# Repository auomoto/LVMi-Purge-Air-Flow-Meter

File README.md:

# LVMi Purge Air Flow Meter
 Differential Pressure Sensor for LVMi Purge Air Flow

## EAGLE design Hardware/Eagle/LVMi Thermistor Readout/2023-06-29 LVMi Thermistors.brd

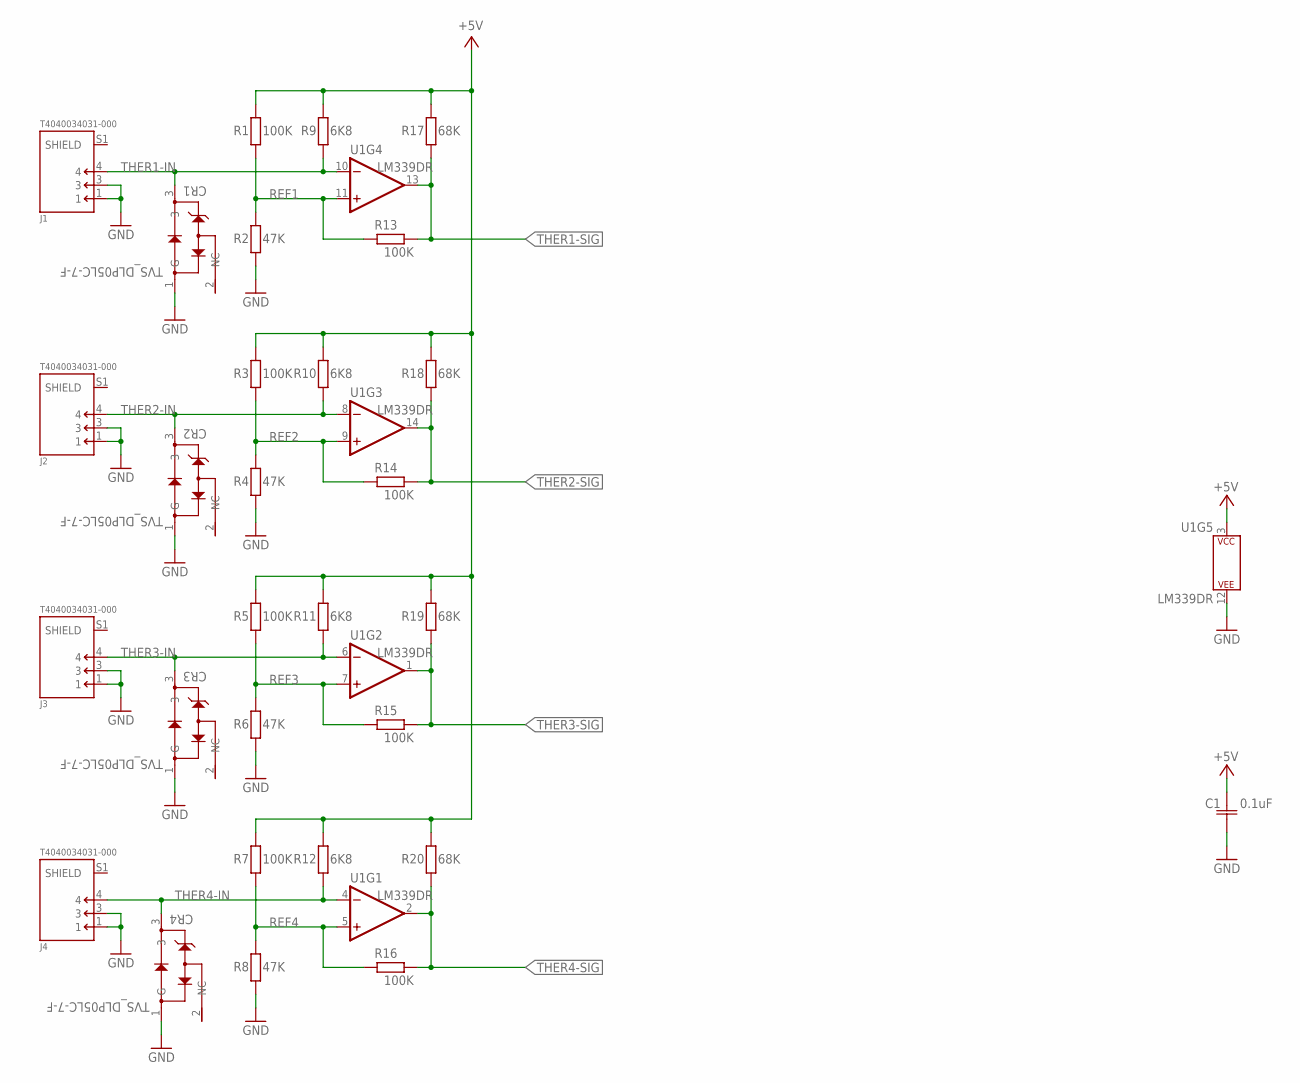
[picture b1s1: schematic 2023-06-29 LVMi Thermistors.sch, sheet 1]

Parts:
C1: 0.1uF; K104K15X7RF5TL2_VIS
CR1, CR2, CR3, CR4: TVS_DLP05LC-7-F; SOT23_DLP05LC_DIO
J1, J2, J3, J4: T4040034031-000; TE_T4040034031-000
R1, R3, R5, R7, R13, R14, R15, R16: 100K; 0207/10
R2, R4, R6, R8: 47K; 0207/10
R9, R10, R11, R12: 6K8; 0207/10
R17, R18, R19, R20: 68K; 0207/10
U1: LM339DR; SOIC127P599X175-14

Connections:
+5V: C1.2, R1.2, R3.2, R5.2, R7.2, R9.2, R10.2, R11.2, R12.2, R17.2, R18.2, R19.2, R20.2, U1.3 (P$V+); also elsewhere on the board
GND: C1.1, CR1.1 (G), CR2.1 (G), CR3.1 (G), CR4.1 (G), J1.1, J1.3, J2.1, J2.3, J3.1, J3.3, J4.1, J4.3, R2.1, R4.1, R6.1, R8.1, U1.12 (P$V-); also elsewhere on the board
REF1: R1.1, R2.2, R13.2, U1.11 (+IN)
REF2: R3.1, R4.2, R14.2, U1.9 (+IN)
REF3: R5.1, R6.2, R15.2, U1.7 (+IN)
REF4: R7.1, R8.2, R16.2, U1.5 (+IN)
THER1-IN: CR1.3, J1.4, R9.1, U1.10 (-IN)
THER1-SIG: R13.1, R17.1, U1.13 (OUT); also elsewhere on the board
THER2-IN: CR2.3, J2.4, R10.1, U1.8 (-IN)
THER2-SIG: R14.1, R18.1, U1.14 (OUT); also elsewhere on the board
THER3-IN: CR3.3, J3.4, R11.1, U1.6 (-IN)
THER3-SIG: R15.1, R19.1, U1.1 (OUT); also elsewhere on the board
THER4-IN: CR4.3, J4.4, R12.1, U1.4 (-IN)
THER4-SIG: R16.1, R20.1, U1.2 (OUT); also elsewhere on the board

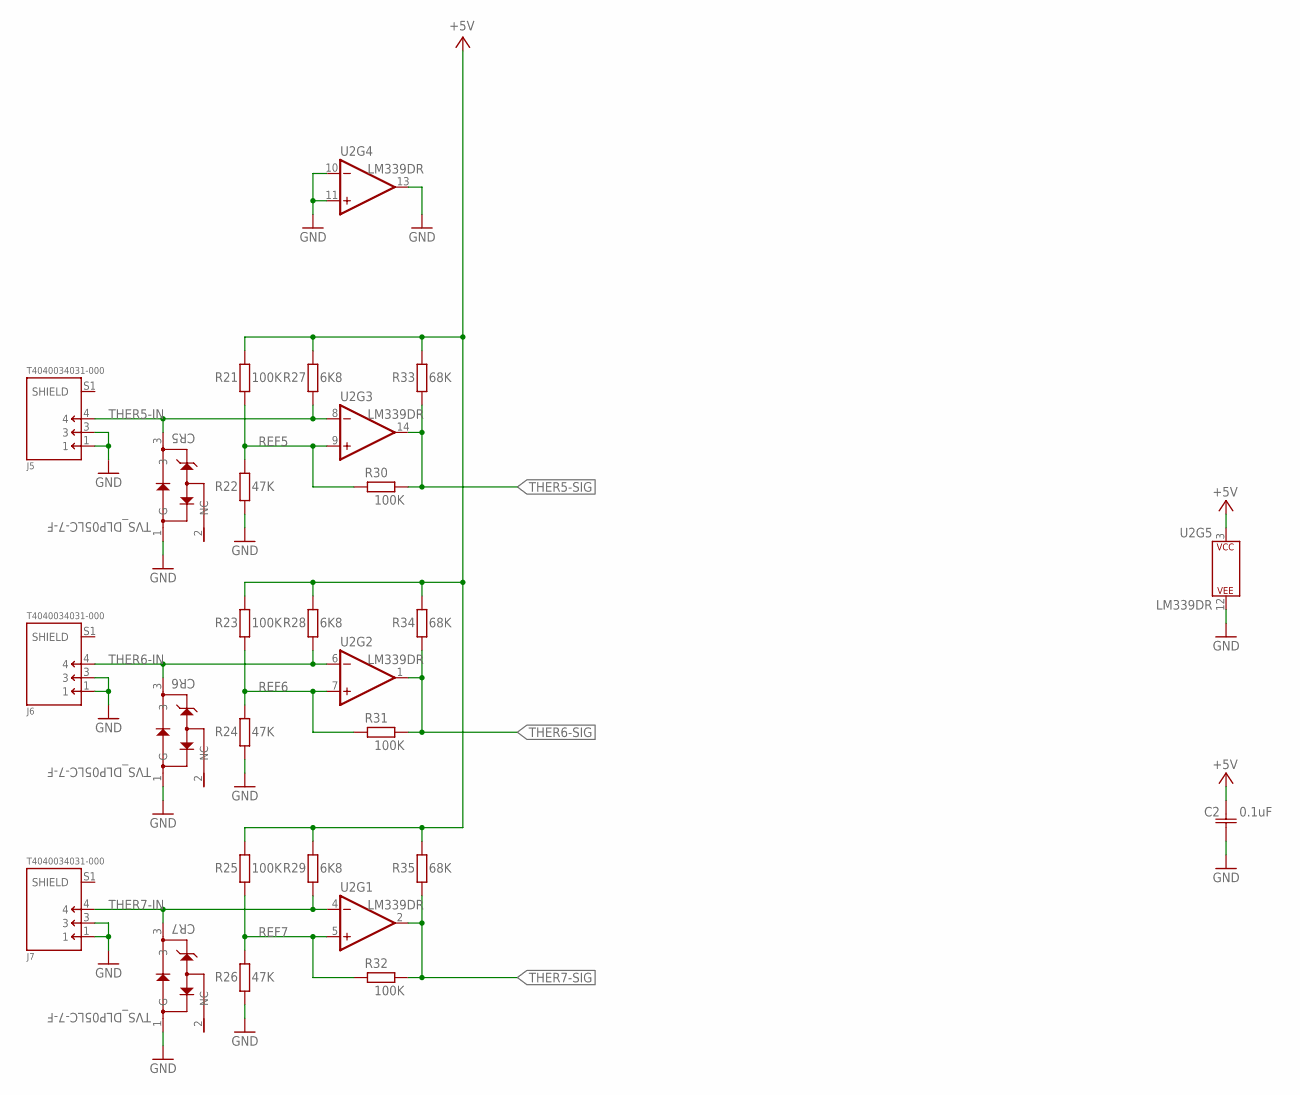
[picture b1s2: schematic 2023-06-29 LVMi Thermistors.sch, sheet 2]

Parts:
C2: 0.1uF; K104K15X7RF5TL2_VIS
CR5, CR6, CR7: TVS_DLP05LC-7-F; SOT23_DLP05LC_DIO
J5, J6, J7: T4040034031-000; TE_T4040034031-000
R21, R23, R25, R30, R31, R32: 100K; 0207/10
R22, R24, R26: 47K; 0207/10
R27, R28, R29: 6K8; 0207/10
R33, R34, R35: 68K; 0207/10
U2: LM339DR; SOIC127P599X175-14

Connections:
+5V: C2.2, R21.2, R23.2, R25.2, R27.2, R28.2, R29.2, R33.2, R34.2, R35.2, U2.3 (P$V+); also elsewhere on the board
GND: C2.1, CR5.1 (G), CR6.1 (G), CR7.1 (G), J5.1, J5.3, J6.1, J6.3, J7.1, J7.3, R22.1, R24.1, R26.1, U2.10 (-IN), U2.11 (+IN), U2.12 (P$V-), U2.13 (OUT); also elsewhere on the board
REF5: R21.1, R22.2, R30.2, U2.9 (+IN)
REF6: R23.1, R24.2, R31.2, U2.7 (+IN)
REF7: R25.1, R26.2, R32.2, U2.5 (+IN)
THER5-IN: CR5.3, J5.4, R27.1, U2.8 (-IN)
THER5-SIG: R30.1, R33.1, U2.14 (OUT); also elsewhere on the board
THER6-IN: CR6.3, J6.4, R28.1, U2.6 (-IN)
THER6-SIG: R31.1, R34.1, U2.1 (OUT); also elsewhere on the board
THER7-IN: CR7.3, J7.4, R29.1, U2.4 (-IN)
THER7-SIG: R32.1, R35.1, U2.2 (OUT); also elsewhere on the board

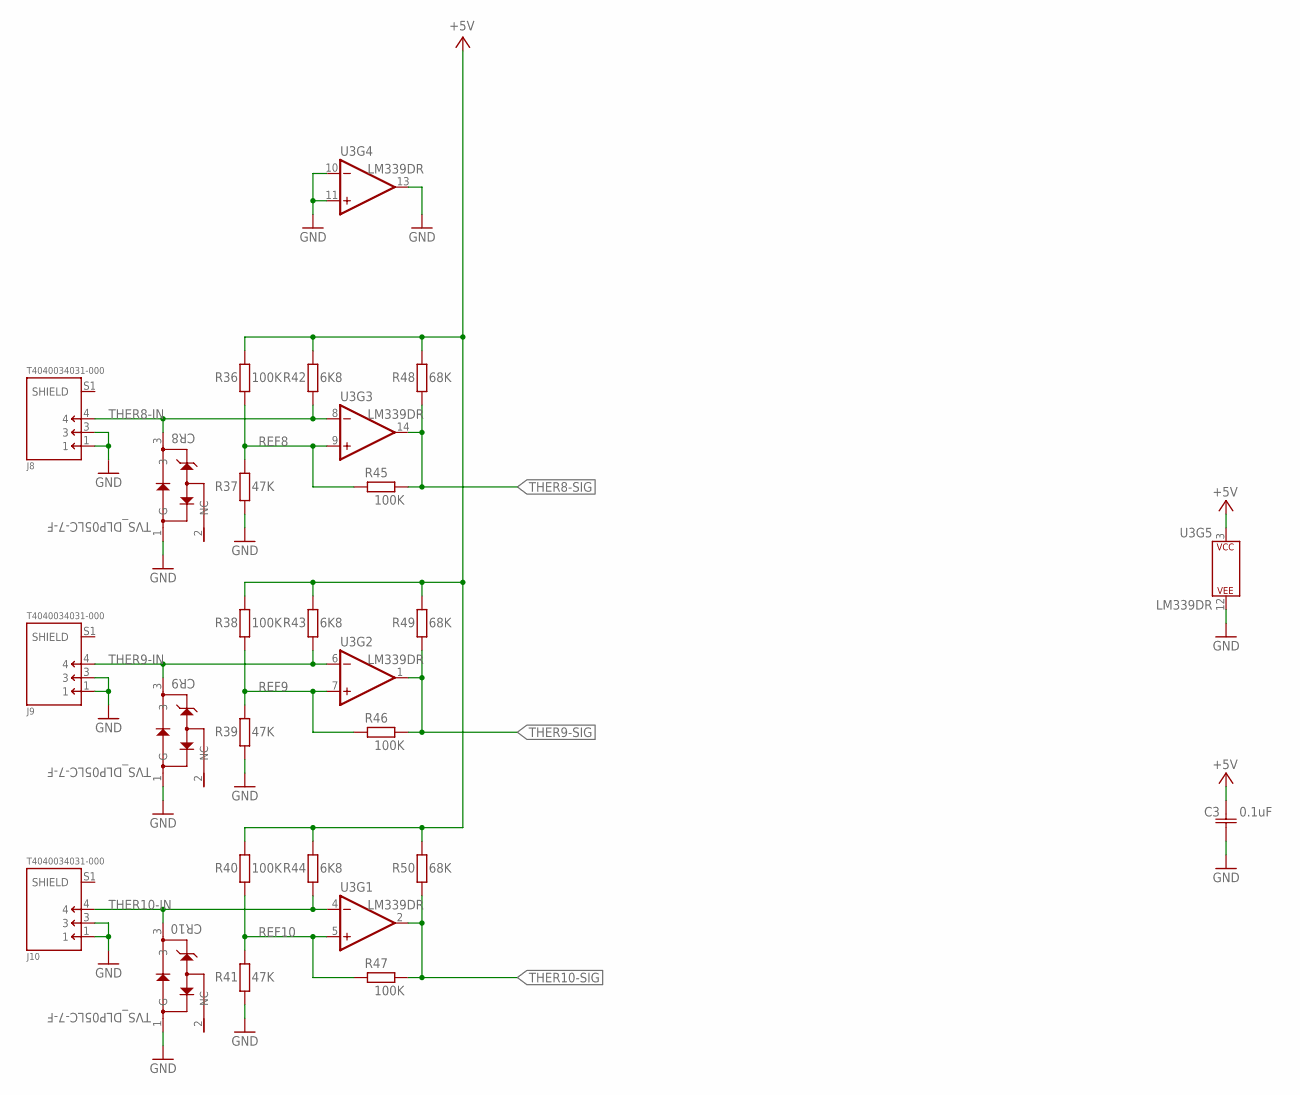
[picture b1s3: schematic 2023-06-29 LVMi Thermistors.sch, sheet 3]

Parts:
C3: 0.1uF; K104K15X7RF5TL2_VIS
CR8, CR9, CR10: TVS_DLP05LC-7-F; SOT23_DLP05LC_DIO
J8, J9, J10: T4040034031-000; TE_T4040034031-000
R36, R38, R40, R45, R46, R47: 100K; 0207/10
R37, R39, R41: 47K; 0207/10
R42, R43, R44: 6K8; 0207/10
R48, R49, R50: 68K; 0207/10
U3: LM339DR; SOIC127P599X175-14

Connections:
+5V: C3.2, R36.2, R38.2, R40.2, R42.2, R43.2, R44.2, R48.2, R49.2, R50.2, U3.3 (P$V+); also elsewhere on the board
GND: C3.1, CR8.1 (G), CR9.1 (G), CR10.1 (G), J8.1, J8.3, J9.1, J9.3, J10.1, J10.3, R37.1, R39.1, R41.1, U3.10 (-IN), U3.11 (+IN), U3.12 (P$V-), U3.13 (OUT); also elsewhere on the board
REF8: R36.1, R37.2, R45.2, U3.9 (+IN)
REF9: R38.1, R39.2, R46.2, U3.7 (+IN)
REF10: R40.1, R41.2, R47.2, U3.5 (+IN)
THER8-IN: CR8.3, J8.4, R42.1, U3.8 (-IN)
THER8-SIG: R45.1, R48.1, U3.14 (OUT); also elsewhere on the board
THER9-IN: CR9.3, J9.4, R43.1, U3.6 (-IN)
THER9-SIG: R46.1, R49.1, U3.1 (OUT); also elsewhere on the board
THER10-IN: CR10.3, J10.4, R44.1, U3.4 (-IN)
THER10-SIG: R47.1, R50.1, U3.2 (OUT); also elsewhere on the board

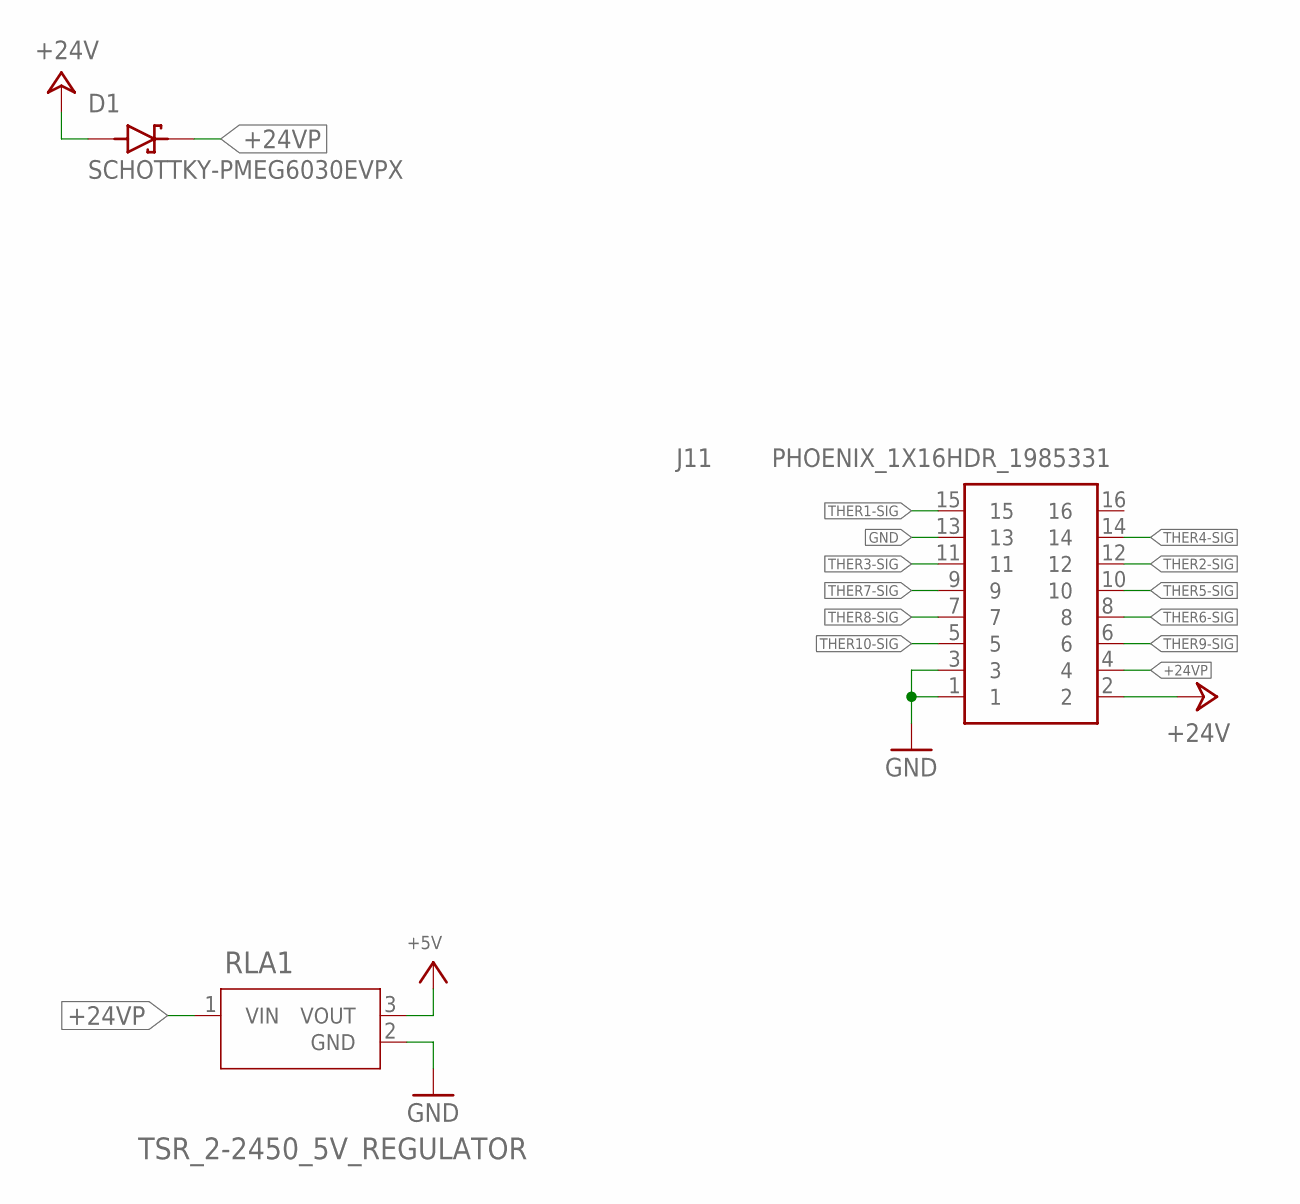
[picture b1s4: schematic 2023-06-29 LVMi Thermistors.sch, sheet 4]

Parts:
D1: SCHOTTKY-PMEG6030EVPX; DIO_PMEG6030EVPX
J11: PHOENIX_1X16HDR_1985331; 1985331
RLA1: TSR_2-2450_5V_REGULATOR; TSR2-SINGLE_TRP

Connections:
+5V: RLA1.3 (VOUT); also elsewhere on the board
+24V: D1.2 (A), J11.2
+24VP: D1.1 (K), J11.4, RLA1.1 (VIN)
GND: J11.1, J11.3, J11.13, RLA1.2 (GND); also elsewhere on the board
THER1-SIG: J11.15; also elsewhere on the board
THER2-SIG: J11.12; also elsewhere on the board
THER3-SIG: J11.11; also elsewhere on the board
THER4-SIG: J11.14; also elsewhere on the board
THER5-SIG: J11.10; also elsewhere on the board
THER6-SIG: J11.8; also elsewhere on the board
THER7-SIG: J11.9; also elsewhere on the board
THER8-SIG: J11.7; also elsewhere on the board
THER9-SIG: J11.6; also elsewhere on the board
THER10-SIG: J11.5; also elsewhere on the board

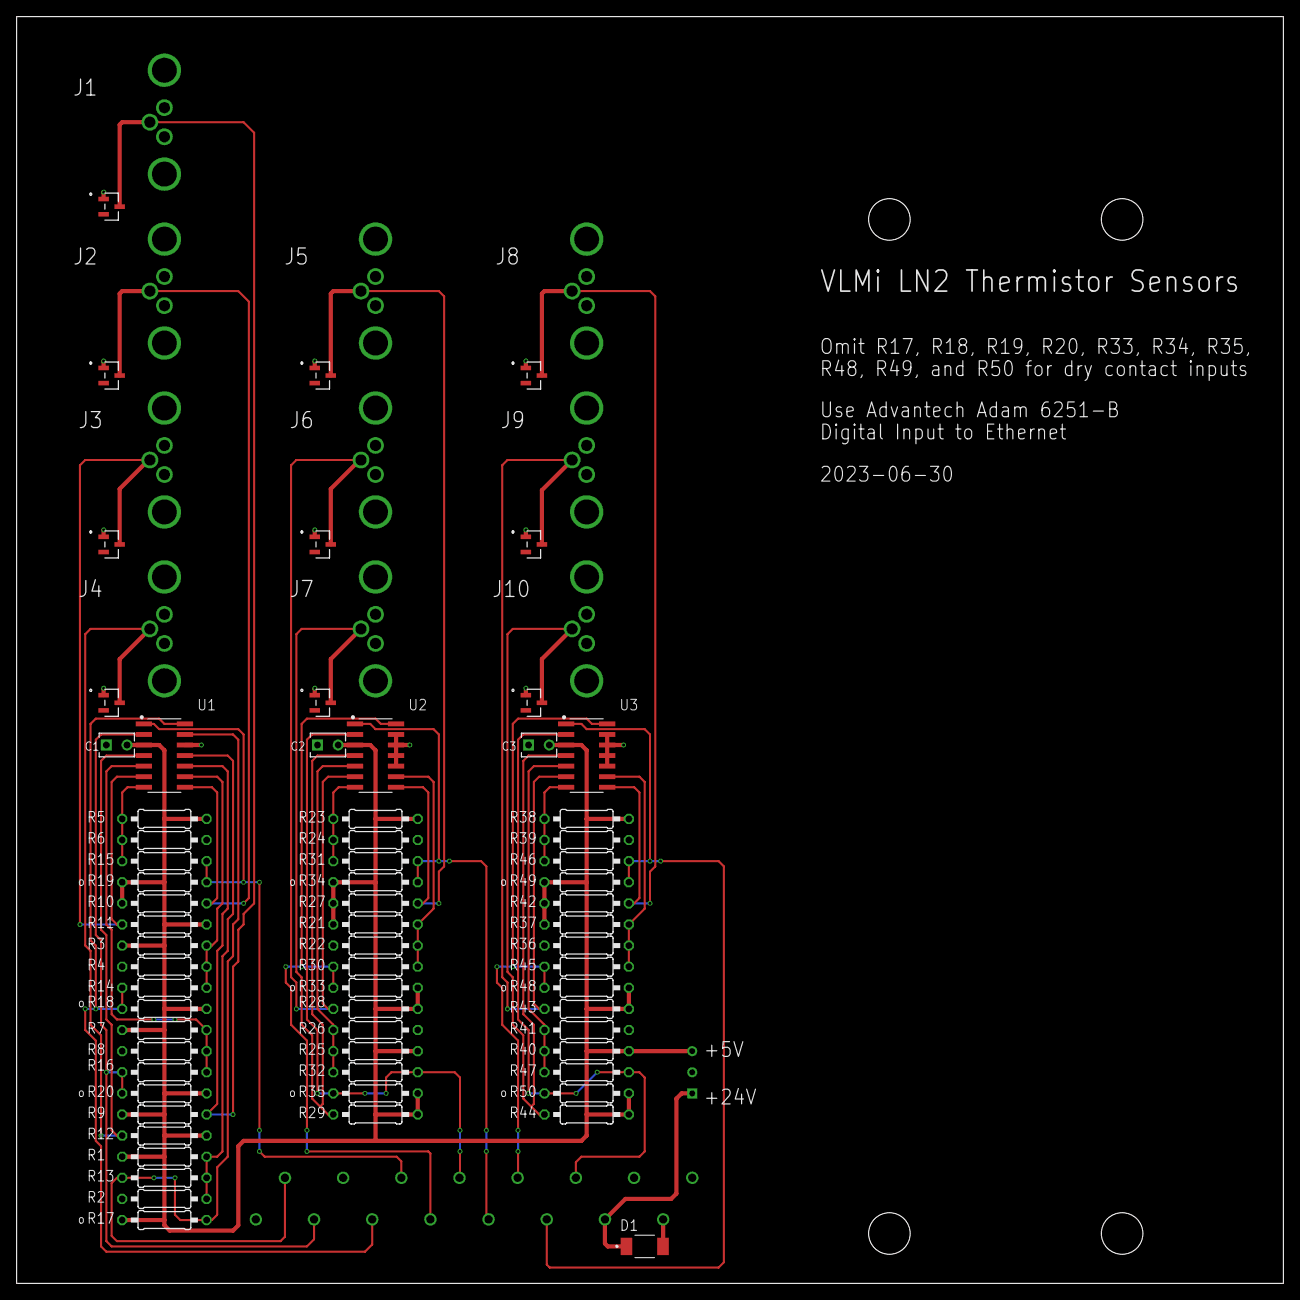
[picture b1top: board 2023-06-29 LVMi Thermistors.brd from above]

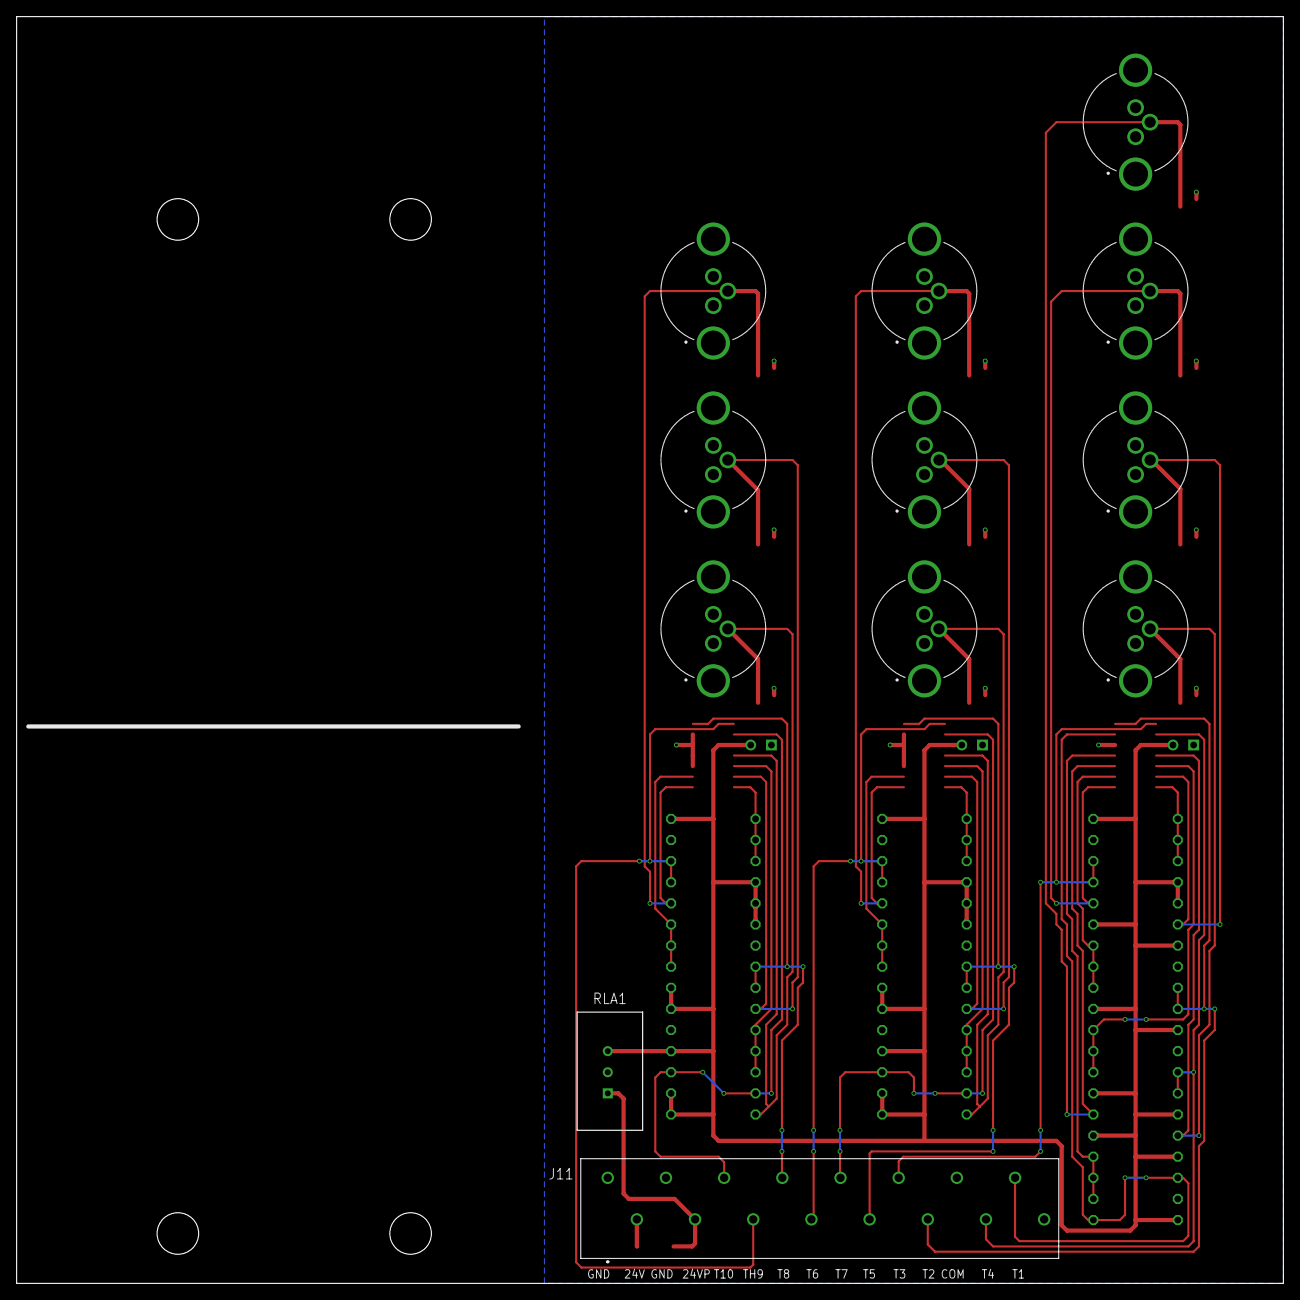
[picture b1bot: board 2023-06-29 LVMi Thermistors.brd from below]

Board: 2 copper layers, 152.4 x 152.4 mm, 79 parts (2 on the bottom side), 34 nets.

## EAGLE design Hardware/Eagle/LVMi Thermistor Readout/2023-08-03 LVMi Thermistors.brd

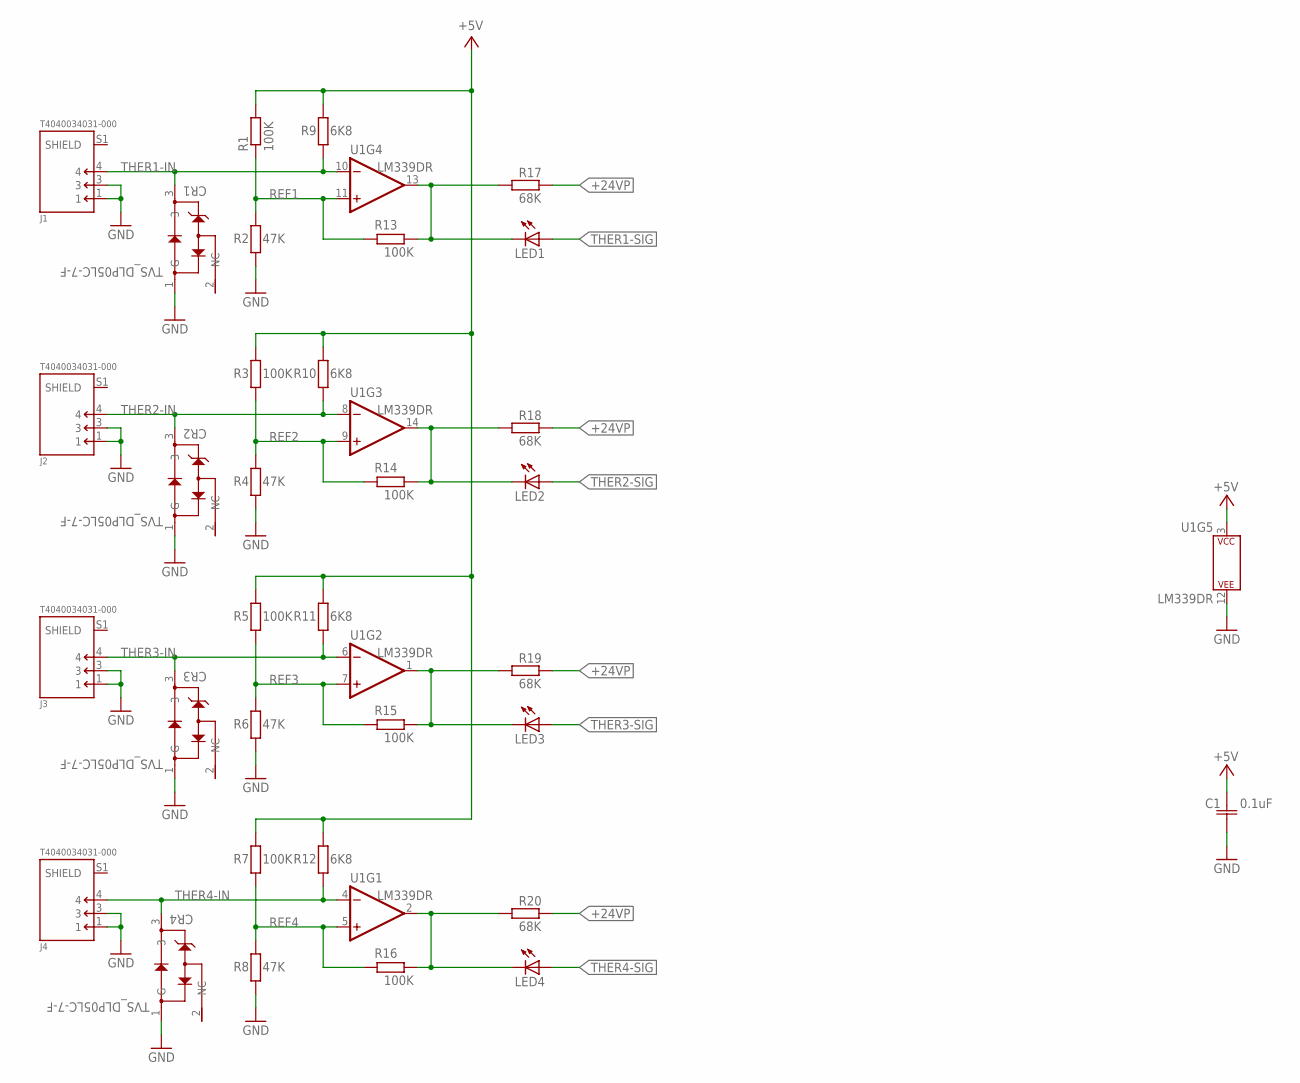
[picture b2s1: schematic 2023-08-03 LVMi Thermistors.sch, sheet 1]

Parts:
C1: 0.1uF; K104K15X7RF5TL2_VIS
CR1, CR2, CR3, CR4: TVS_DLP05LC-7-F; SOT23_DLP05LC_DIO
J1, J2, J3, J4: T4040034031-000; TE_T4040034031-000
LED1, LED2, LED3, LED4: LED5MM
R1, R3, R5, R7, R13, R14, R15, R16: 100K; 0204/7
R2, R4, R6, R8: 47K; 0204/7
R9, R10, R11, R12: 6K8; 0204/7
R17, R18, R19, R20: 68K; 0204/7
U1: LM339DR; SOIC127P599X175-14

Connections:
+5V: C1.2, R1.2, R3.2, R5.2, R7.2, R9.2, R10.2, R11.2, R12.2, U1.3 (P$V+); also elsewhere on the board
+24VP: R17.1, R18.1, R19.1, R20.2; also elsewhere on the board
GND: C1.1, CR1.1 (G), CR2.1 (G), CR3.1 (G), CR4.1 (G), J1.1, J1.3, J2.1, J2.3, J3.1, J3.3, J4.1, J4.3, R2.1, R4.1, R6.1, R8.1, U1.12 (P$V-); also elsewhere on the board
REF1: R1.1, R2.2, R13.2, U1.11 (+IN)
REF2: R3.1, R4.2, R14.2, U1.9 (+IN)
REF3: R5.1, R6.2, R15.2, U1.7 (+IN)
REF4: R7.1, R8.2, R16.2, U1.5 (+IN)
THER1-IN: CR1.3, J1.4, LED1.K (C), R9.1, R13.1, R17.2, U1.10 (-IN), U1.13 (OUT)
THER1-SIG: LED1.A; also elsewhere on the board
THER2-IN: CR2.3, J2.4, LED2.K (C), R10.1, R14.1, R18.2, U1.8 (-IN), U1.14 (OUT)
THER2-SIG: LED2.A; also elsewhere on the board
THER3-IN: CR3.3, J3.4, LED3.K (C), R11.1, R15.1, R19.2, U1.1 (OUT), U1.6 (-IN)
THER3-SIG: LED3.A; also elsewhere on the board
THER4-IN: CR4.3, J4.4, LED4.K (C), R12.1, R16.1, R20.1, U1.2 (OUT), U1.4 (-IN)
THER4-SIG: LED4.A; also elsewhere on the board

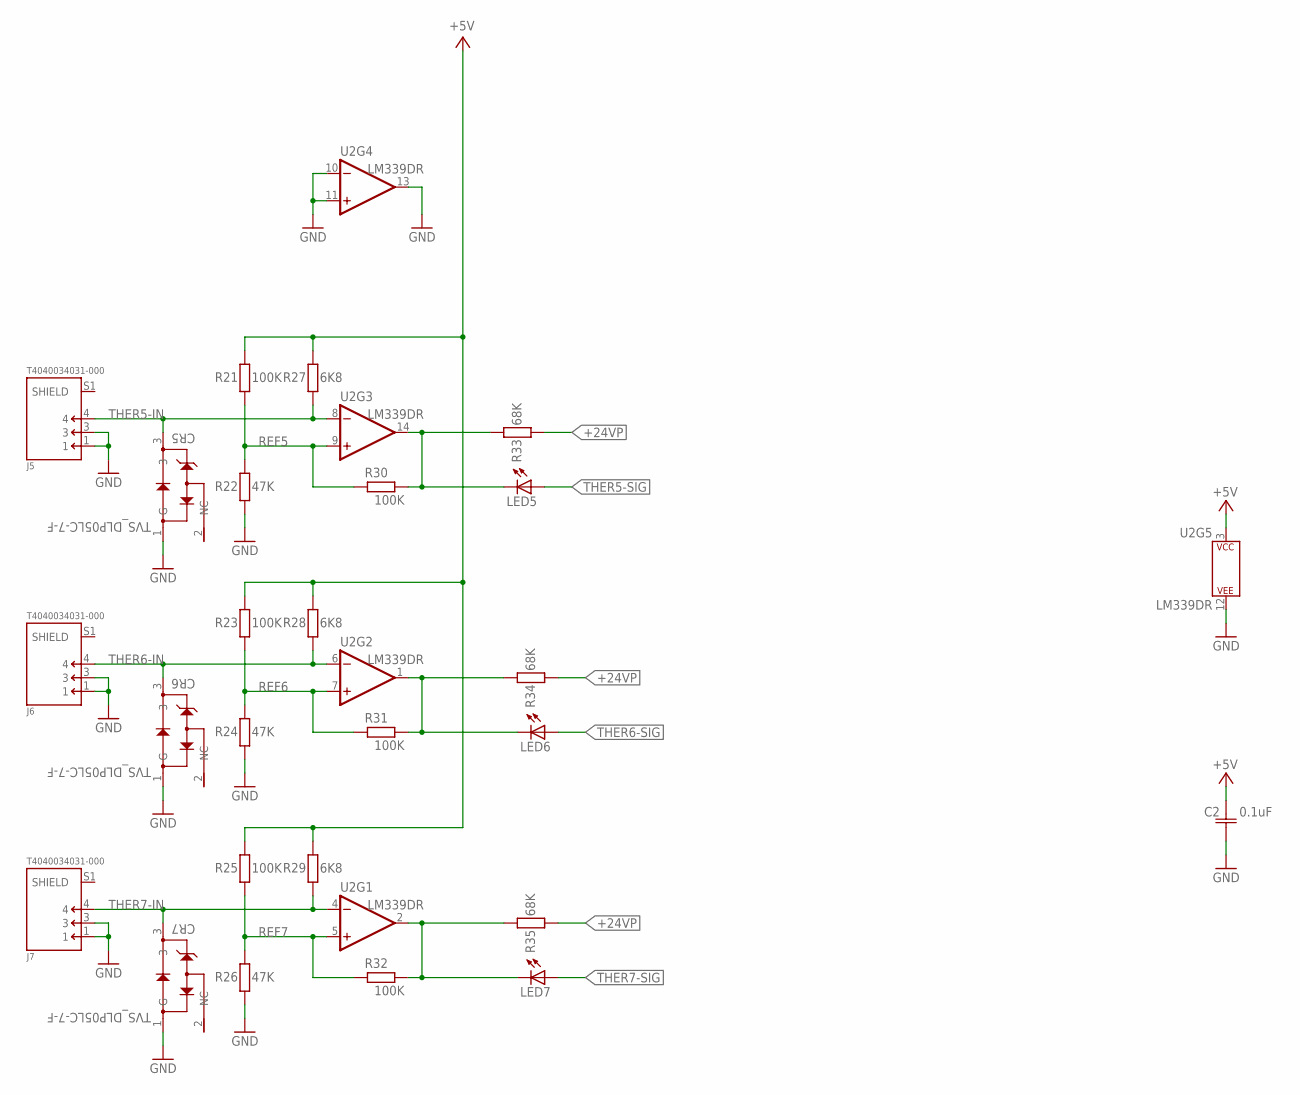
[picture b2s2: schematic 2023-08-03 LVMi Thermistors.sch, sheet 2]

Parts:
C2: 0.1uF; K104K15X7RF5TL2_VIS
CR5, CR6, CR7: TVS_DLP05LC-7-F; SOT23_DLP05LC_DIO
J5, J6, J7: T4040034031-000; TE_T4040034031-000
LED5, LED6, LED7: LED5MM
R21, R23, R25, R30, R31, R32: 100K; 0204/7
R22, R24, R26: 47K; 0204/7
R27, R28, R29: 6K8; 0204/7
R33, R34, R35: 68K; 0204/7
U2: LM339DR; SOIC127P599X175-14

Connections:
+5V: C2.2, R21.2, R23.2, R25.2, R27.2, R28.2, R29.2, U2.3 (P$V+); also elsewhere on the board
+24VP: R33.1, R34.1, R35.1; also elsewhere on the board
GND: C2.1, CR5.1 (G), CR6.1 (G), CR7.1 (G), J5.1, J5.3, J6.1, J6.3, J7.1, J7.3, R22.1, R24.1, R26.1, U2.10 (-IN), U2.11 (+IN), U2.12 (P$V-), U2.13 (OUT); also elsewhere on the board
REF5: R21.1, R22.2, R30.2, U2.9 (+IN)
REF6: R23.1, R24.2, R31.2, U2.7 (+IN)
REF7: R25.1, R26.2, R32.2, U2.5 (+IN)
THER5-IN: CR5.3, J5.4, LED5.K (C), R27.1, R30.1, R33.2, U2.8 (-IN), U2.14 (OUT)
THER5-SIG: LED5.A; also elsewhere on the board
THER6-IN: CR6.3, J6.4, LED6.K (C), R28.1, R31.1, R34.2, U2.1 (OUT), U2.6 (-IN)
THER6-SIG: LED6.A; also elsewhere on the board
THER7-IN: CR7.3, J7.4, LED7.K (C), R29.1, R32.1, R35.2, U2.2 (OUT), U2.4 (-IN)
THER7-SIG: LED7.A; also elsewhere on the board

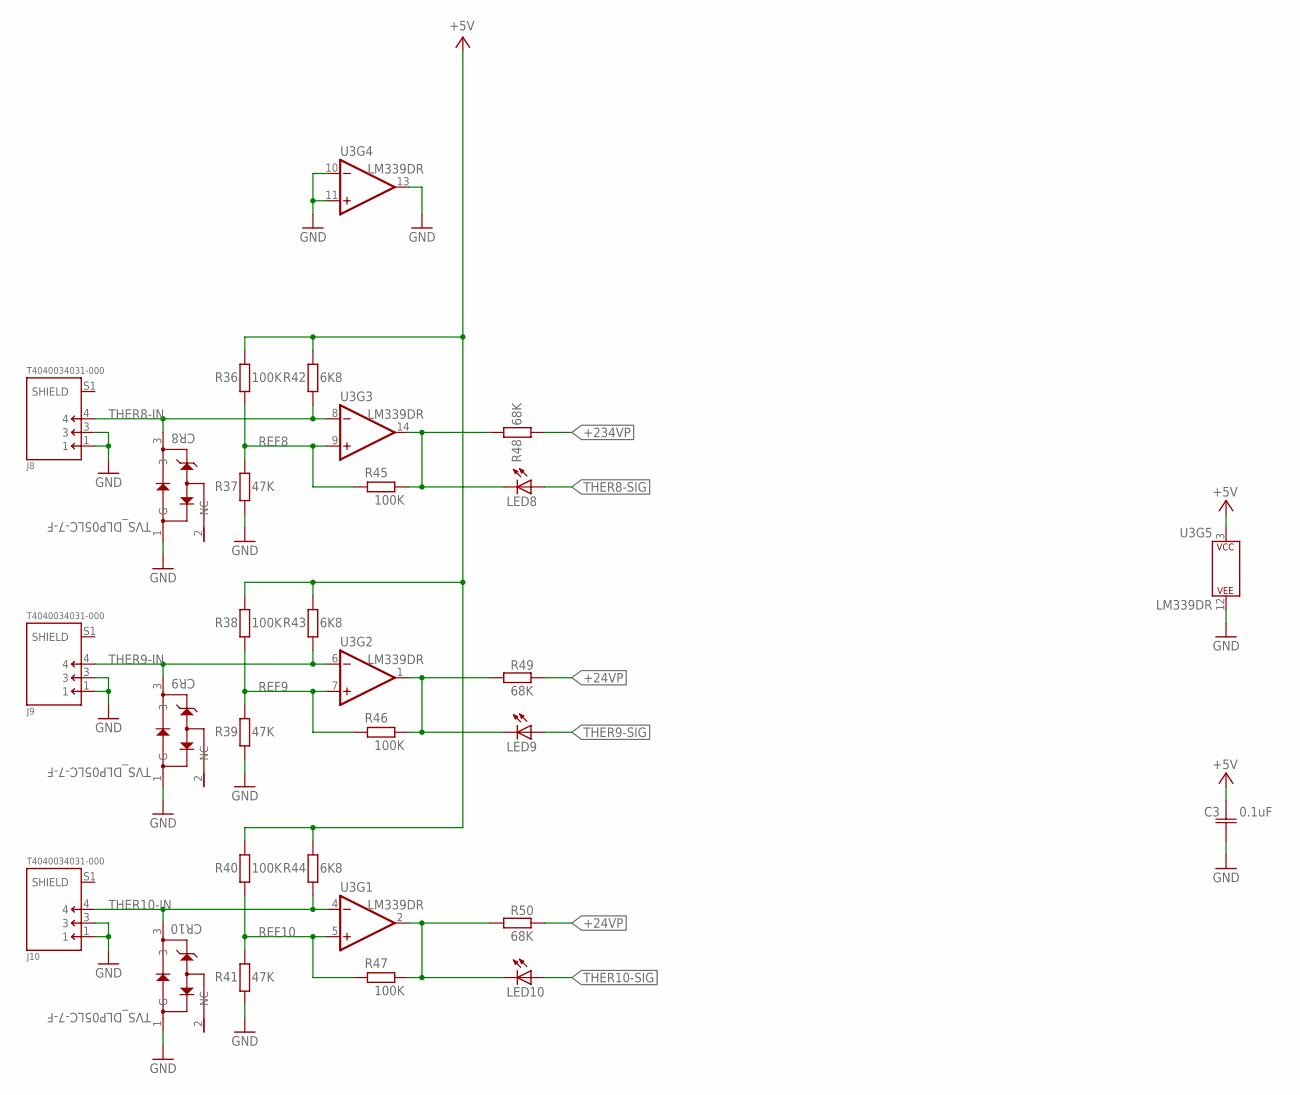
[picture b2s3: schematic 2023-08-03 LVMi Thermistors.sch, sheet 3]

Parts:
C3: 0.1uF; K104K15X7RF5TL2_VIS
CR8, CR9, CR10: TVS_DLP05LC-7-F; SOT23_DLP05LC_DIO
J8, J9, J10: T4040034031-000; TE_T4040034031-000
LED8, LED9, LED10: LED5MM
R36, R38, R40, R45, R46, R47: 100K; 0204/7
R37, R39, R41: 47K; 0204/7
R42, R43, R44: 6K8; 0204/7
R48, R49, R50: 68K; 0204/7
U3: LM339DR; SOIC127P599X175-14

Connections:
+5V: C3.2, R36.2, R38.2, R40.2, R42.2, R43.2, R44.2, U3.3 (P$V+); also elsewhere on the board
+24VP: R49.1, R50.1; also elsewhere on the board
+234VP: R48.1
GND: C3.1, CR8.1 (G), CR9.1 (G), CR10.1 (G), J8.1, J8.3, J9.1, J9.3, J10.1, J10.3, R37.1, R39.1, R41.1, U3.10 (-IN), U3.11 (+IN), U3.12 (P$V-), U3.13 (OUT); also elsewhere on the board
REF8: R36.1, R37.2, R45.2, U3.9 (+IN)
REF9: R38.1, R39.2, R46.2, U3.7 (+IN)
REF10: R40.1, R41.2, R47.2, U3.5 (+IN)
THER8-IN: CR8.3, J8.4, LED8.K (C), R42.1, R45.1, R48.2, U3.8 (-IN), U3.14 (OUT)
THER8-SIG: LED8.A; also elsewhere on the board
THER9-IN: CR9.3, J9.4, LED9.K (C), R43.1, R46.1, R49.2, U3.1 (OUT), U3.6 (-IN)
THER9-SIG: LED9.A; also elsewhere on the board
THER10-IN: CR10.3, J10.4, LED10.K (C), R44.1, R47.1, R50.2, U3.2 (OUT), U3.4 (-IN)
THER10-SIG: LED10.A; also elsewhere on the board

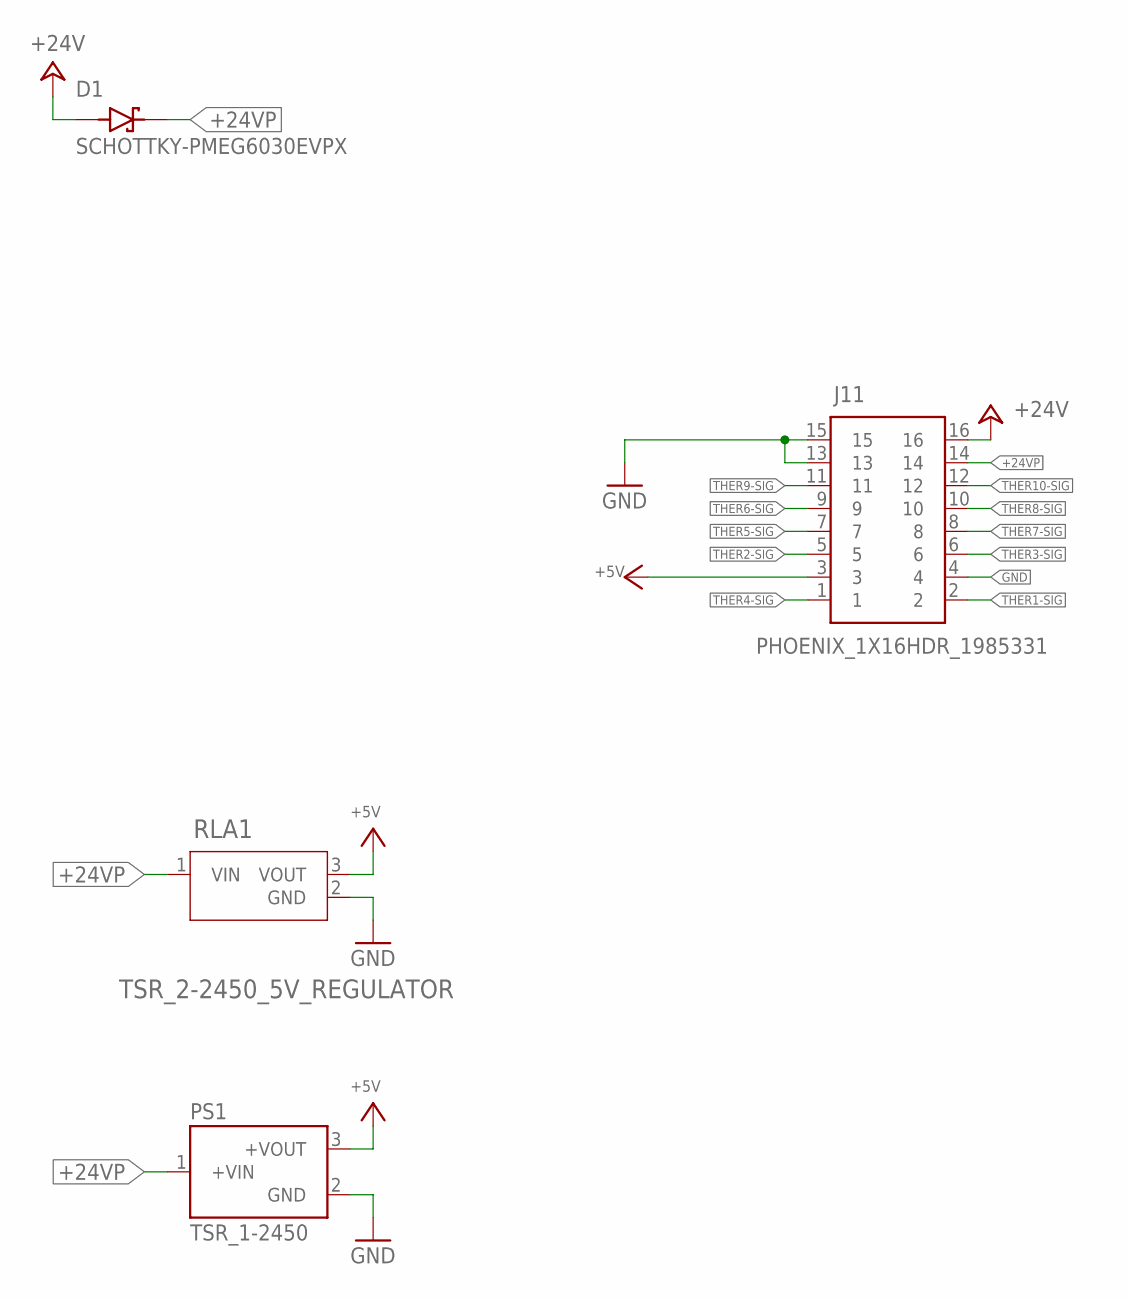
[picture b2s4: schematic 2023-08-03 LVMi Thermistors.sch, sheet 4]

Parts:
D1: SCHOTTKY-PMEG6030EVPX; DIO_PMEG6030EVPX
J11: PHOENIX_1X16HDR_1985331; 1985331
PS1: TSR_1-2450; CONV_TSR_1-2450
RLA1: TSR_2-2450_5V_REGULATOR; TSR2-SINGLE_TRP

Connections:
+5V: J11.3, PS1.3 (+VOUT), RLA1.3 (VOUT); also elsewhere on the board
+24V: D1.2 (A), J11.16
+24VP: D1.1 (K), J11.14, PS1.1 (+VIN), RLA1.1 (VIN); also elsewhere on the board
GND: J11.4, J11.13, J11.15, PS1.2 (GND), RLA1.2 (GND); also elsewhere on the board
THER1-SIG: J11.2; also elsewhere on the board
THER2-SIG: J11.5; also elsewhere on the board
THER3-SIG: J11.6; also elsewhere on the board
THER4-SIG: J11.1; also elsewhere on the board
THER5-SIG: J11.7; also elsewhere on the board
THER6-SIG: J11.9; also elsewhere on the board
THER7-SIG: J11.8; also elsewhere on the board
THER8-SIG: J11.10; also elsewhere on the board
THER9-SIG: J11.11; also elsewhere on the board
THER10-SIG: J11.12; also elsewhere on the board

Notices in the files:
parts and their libraries:
COPYRIGHT: Copyright (C) 2022 Ultra Librarian. All rights reserved.
COPYRIGHT: Copyright (C) 2023 Ultra Librarian. All rights reserved.
